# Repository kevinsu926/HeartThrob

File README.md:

# Heartthrob

A heart-shaped ECG board that turns your heartbeat into sound. Touch the two gold electrodes and it plays your ECG as a high-pitched tone, which a phone or laptop can decode using its microphone. It has no Bluetooth, no Wi-Fi and no firmware. 

## How it works

```mermaid
flowchart LR
    A[Fingers on<br/>electrodes] --> B[AD8233<br/>ECG amplifier]
    B --> C[LTC6990<br/>oscillator]
    C --> D[Piezo<br/>~18.5 kHz tone]
    D --> E[Phone / laptop<br/>microphone]
```

1. **Pick up the signal.** One finger from each hand rests on the gold electrodes on each side of the heart. The tiny voltage your heart produces appears between them.
2. **Amplify it.** An AD8233 ECG chip amplifies and filters that signal into a clean waveform.
3. **Turn it into a tone.** The waveform controls an LTC6990 oscillator, so the pitch of an 18.5 kHz tone rises and falls with each heartbeat.
4. **Play it.** A small piezo plays the tone. It is high enough that most adults can't hear it, but phone microphones can.
5. **Decode it.** A phone or laptop listens to the tone, tracks its pitch, and turns it back into a live ECG trace and heart rate.

<p align="center">
  <picture>
    <source media="(prefers-color-scheme: dark)" srcset="hardware/Heartthrob/illustrations/sample-waveform-dark.png">
    
  </picture>
</p>

The top trace is what the phone shows: P, QRS and T waves for each beat, with heart rate taken from the time between R peaks. The bottom trace is the same signal as the microphone hears it: a tone near 18.5 kHz whose pitch rises and falls with the ECG. (Simulated example.)

When nobody is touching the electrodes, the board detects that the leads are off and switches the oscillator off to save battery. 

## Power

The board runs on a small 1S LiPo battery soldered to pads on the back, and charges over USB-C. A 3.0 V regulator powers the circuit, and a P-FET protects it if the battery is connected backwards.

## Project structure

- `hardware/Heartthrob/`
  KiCad 10 project: schematic, 4-layer PCB layout, design rules and custom footprints. Open `Heartthrob.kicad_pro`.
- `hardware/Heartthrob/Render/`
  3D renders of the front and back.
- `hardware/Heartthrob/Documentation/`
  Schematic PDF, per-layer PCB plots, and earlier design snapshots in `Archive/`.
- `hardware/Heartthrob/illustrations/`
  Figures used in this README.

> **Note:** This is a hobby project, not a medical device. Don't use it for diagnosis, and don't wear it while it's plugged in to charge.

## Credits

Based on [SiBowald's ECG PCB business card](https://github.com/SiBowald/ecg-pcb-business-card), redesigned by Kevin Su as a rechargeable, heart-shaped board.

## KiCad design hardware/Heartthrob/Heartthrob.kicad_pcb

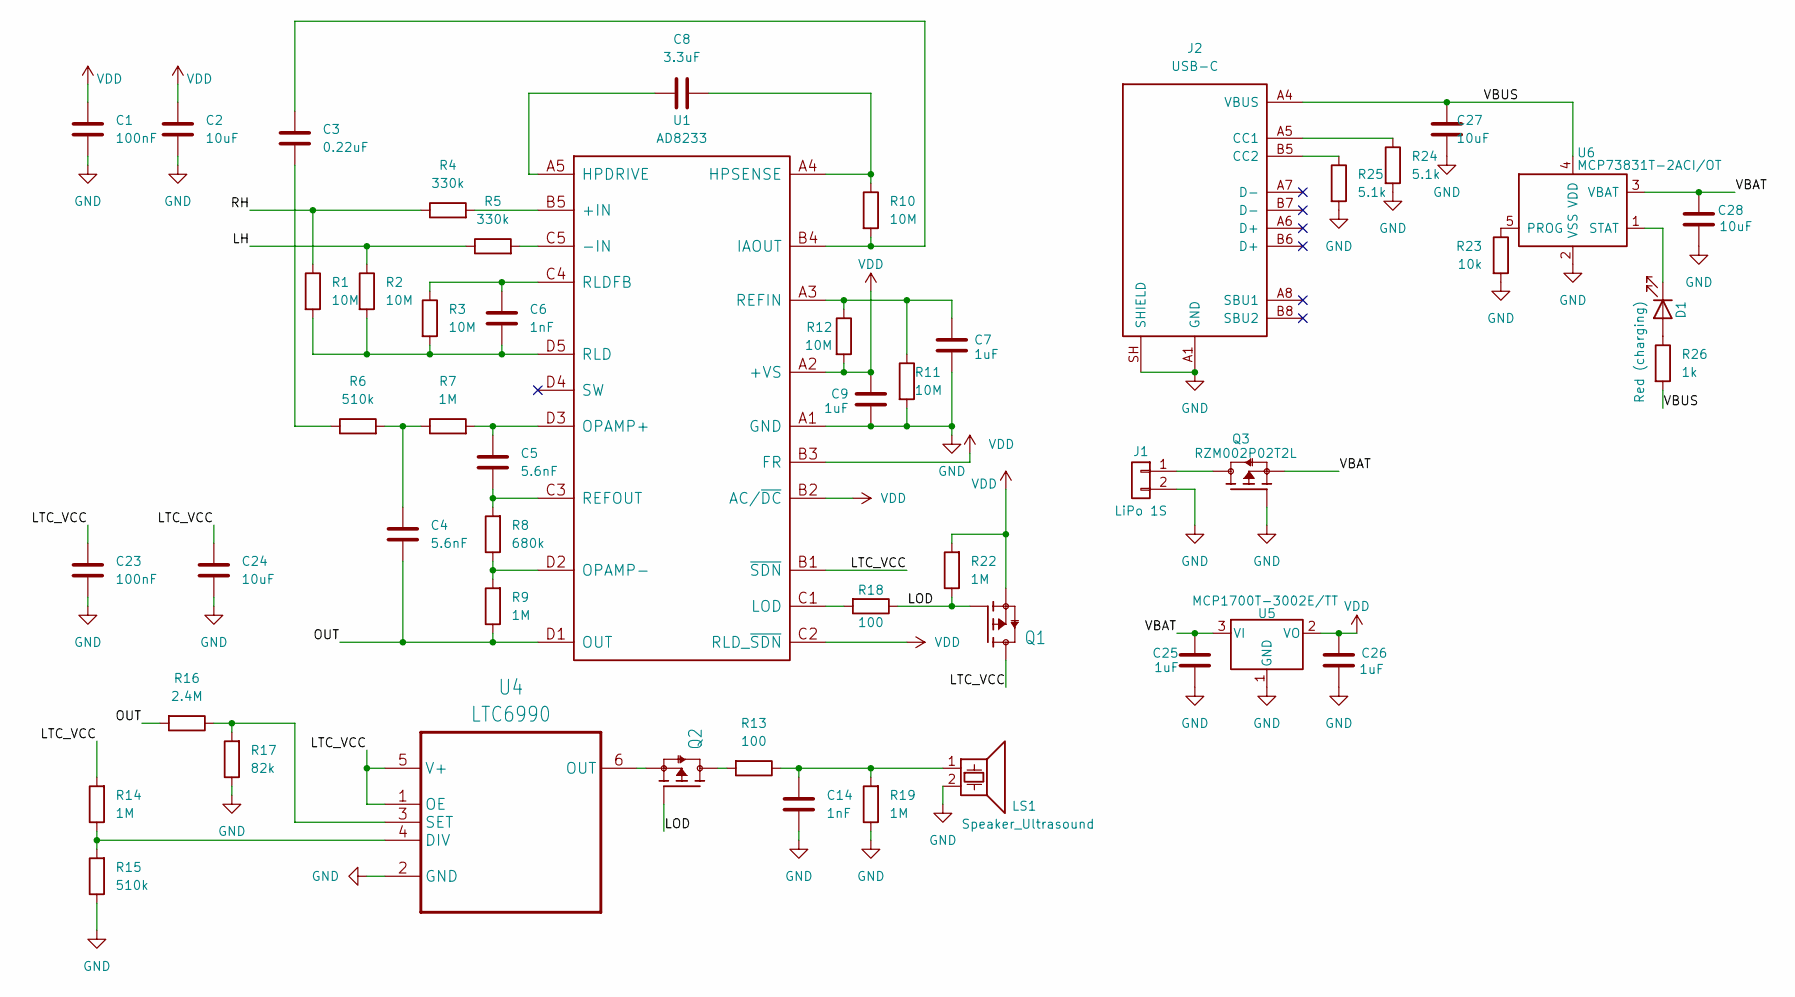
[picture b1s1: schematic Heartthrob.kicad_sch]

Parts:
C1, C23: 100nF; C_0402_1005Metric; Part Name 100nF 16V Ceramic Cap; LCSC C85857
C2, C24, C27, C28: 10uF; C_0402_1005Metric; Part Name 10uF 6.3V Ceramic Cap; LCSC C412251
C3: 0.22uF; C_0402_1005Metric; Part Name 220nF 16V Ceramic Cap; LCSC C126524
C4, C5: 5.6nF; C_0402_1005Metric; Part Name CAP CER 5.6nF 50V C0G 0402; LCSC C3878619
C6, C14: 1nF; C_0402_1005Metric; Part Name 1nF 50V Ceramic Cap; LCSC C76947
C7, C9, C25, C26: 1uF; C_0402_1005Metric; Part Name 1uF 6.3V Ceramic Cap; LCSC C2167130
C8: 3.3uF; C_0402_1005Metric; Part Name 10V 3.3uF X5R ±10% 0402 Ceramic Capacit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; LCSC C695126
D1: Red (charging); LED_0603_1608Metric; Part Number KT-0603R; LCSC C2286
J1: LiPo 1S; LiPo_SMD_Pads_2x3mm_P4mm
J2: USB-C; USB_C_Receptacle_HRO_TYPE-C-31-M-12; Part Number TYPE-C-31-M-12
LS1: Speaker_Ultrasound; Piezo_12mm; Part Name BUZZER ELEMENT STD 18.5 KHZ 12MM
Q1, Q2, Q3: RZM002P02T2L; SOT-723; Part Name MOSFET P-CH 20V 200MA VMT3
R1, R2, R3, R10, R11, R12: 10M; R_0201_0603Metric; Part Name 10M Film Resistor ±1% 0,05W; LCSC C469663
R4, R5: 330k; R_0201_0603Metric; Part Name 330KΩ ±1% 1/20W ±200ppm/℃; LCSC C142017
R6, R15: 510k; R_0201_0603Metric; Part Name 510KΩ ±1% 1/20W ±200ppm/℃; LCSC C295805
R7, R9, R14, R19, R22: 1M; R_0201_0603Metric; Part Name 1M Film Resistor ±1% 1/20W ±200ppm/℃; LCSC C295786
R8: 680k; R_0201_0603Metric; Part Name 680KΩ ±1% 1/20W ±200ppm/℃; LCSC C226598
R13, R18: 100; R_0201_0603Metric; Part Name 100Ω ±1% 1/20W ±200ppm/℃; LCSC C77623
R16: 2.4M; R_0201_0603Metric; Part Name 2.4M Film Resistor ±1% 50mW; LCSC C474580
R17: 82k; R_0201_0603Metric; Part Name 82k Film Resistor ±1% 1/20W ±200ppm/℃; LCSC C273288
R23: 10k; R_0201_0603Metric; Part Number RC0201FR-0710KL; LCSC C106225
R24, R25: 5.1k; R_0201_0603Metric; Part Number RC0201FR-075K1L; LCSC C274341
R26: 1k; R_0201_0603Metric; Part Number RC0201FR-071KL; LCSC C138165
U1: AD8233; 20-WLCPS-2MMX1.7MM
U4: LTC6990; SOT95P280X100-6N; Part Name Oszillator - Silizium IC 488Hz bis 2MHz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; LCSC C581032
U5: MCP1700T-3002E/TT; SOT-23; Part Number MCP1700T-3002E/TT
U6: MCP73831T-2ACI/OT; SOT-23-5; Part Number MCP73831T-2ACI/OT

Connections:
/LH: R2.1, R5.1
/LOD: Q1.1 (G), Q2.1 (G), R18.1, R22.1
/LTC_VCC: C23.2, C24.2, Q1.3 (D), R14.2, U1.B1 (~SDN), U4.1 (OE), U4.5 (V+)
/OUT: C4.1, R9.1, R16.2, U1.D1 (OUT)
/RH: R1.1, R4.1
/VBAT: C25.1, C28.1, Q3.2 (S), U5.3 (VI), U6.3 (VBAT)
/VBUS: C27.1, J2.A4 (VBUS), J2.A9 (VBUS), J2.B4 (VBUS), J2.B9 (VBUS), R26.2, U6.4 (VDD)
GND: C1.1, C2.1, C7.1, C9.1, C14.1, C23.1, C24.1, C25.2, C26.2, C27.2, C28.2, J1.2, J2.A1 (GND), J2.A12 (GND), J2.B1 (GND), J2.B12 (GND), J2.SH (SHIELD), LS1.2, Q3.1 (G), R11.2, R15.1, R17.1, R19.1, R23.2, R24.2, R25.2, U1.A1 (GND), U4.2 (GND), U5.1 (GND), U6.2 (VSS)
unnamed: C3.1, R6.1
unnamed: C4.2, R6.2, R7.1
unnamed: C14.2, LS1.1, R13.1, R19.2
unnamed: D1.2 (A), R26.1
unnamed: D1.1 (K), U6.1 (STAT)
unnamed: J1.1, Q3.3 (D)
unnamed: J2.A5 (CC1), R24.1
unnamed: J2.B5 (CC2), R25.1
unnamed: Q2.3 (D), R13.2
unnamed: Q2.2 (S), U4.6 (OUT)
unnamed: R4.2, U1.B5 (+IN)
unnamed: R5.2, U1.C5 (-IN)
unnamed: C8.1, U1.A5 (HPDRIVE)
unnamed: C8.2, R10.1, U1.A4 (HPSENSE)
unnamed: C3.2, R10.2, U1.B4 (IAOUT)
unnamed: R18.2, U1.C1 (LOD)
unnamed: C5.2, R7.2, U1.D3 (OPAMP+)
unnamed: R8.1, R9.2, U1.D2 (OPAMP-)
unnamed: C7.2, R11.1, R12.1, U1.A3 (REFIN)
unnamed: C5.1, R8.2, U1.C3 (REFOUT)
unnamed: C6.1, R1.2, R2.2, R3.2, U1.D5 (RLD)
unnamed: C6.2, R3.1, U1.C4 (RLDFB)
unnamed: R14.1, R15.2, U4.4 (DIV)
unnamed: R16.1, R17.2, U4.3 (SET)
unnamed: R23.1, U6.5 (PROG)
VDD: C1.2, C2.2, C9.2, C26.1, Q1.2 (S), R12.2, R22.2, U1.A2 (+VS), U1.B2 (AC/~DC), U1.B3 (FR), U1.C2 (RLD_~SDN), U5.2 (VO)

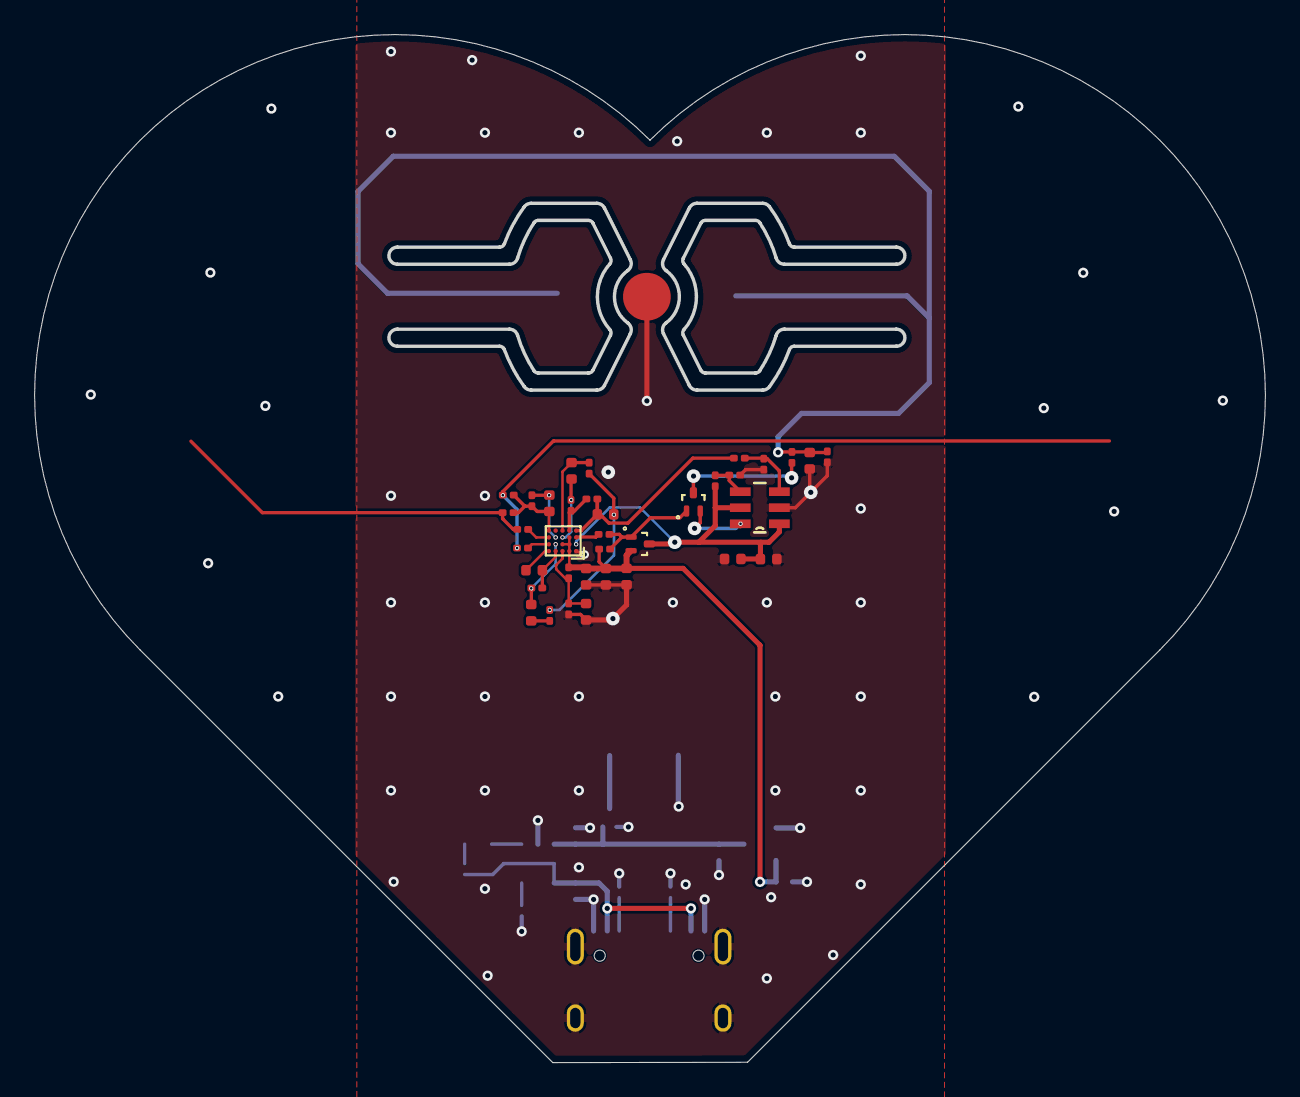
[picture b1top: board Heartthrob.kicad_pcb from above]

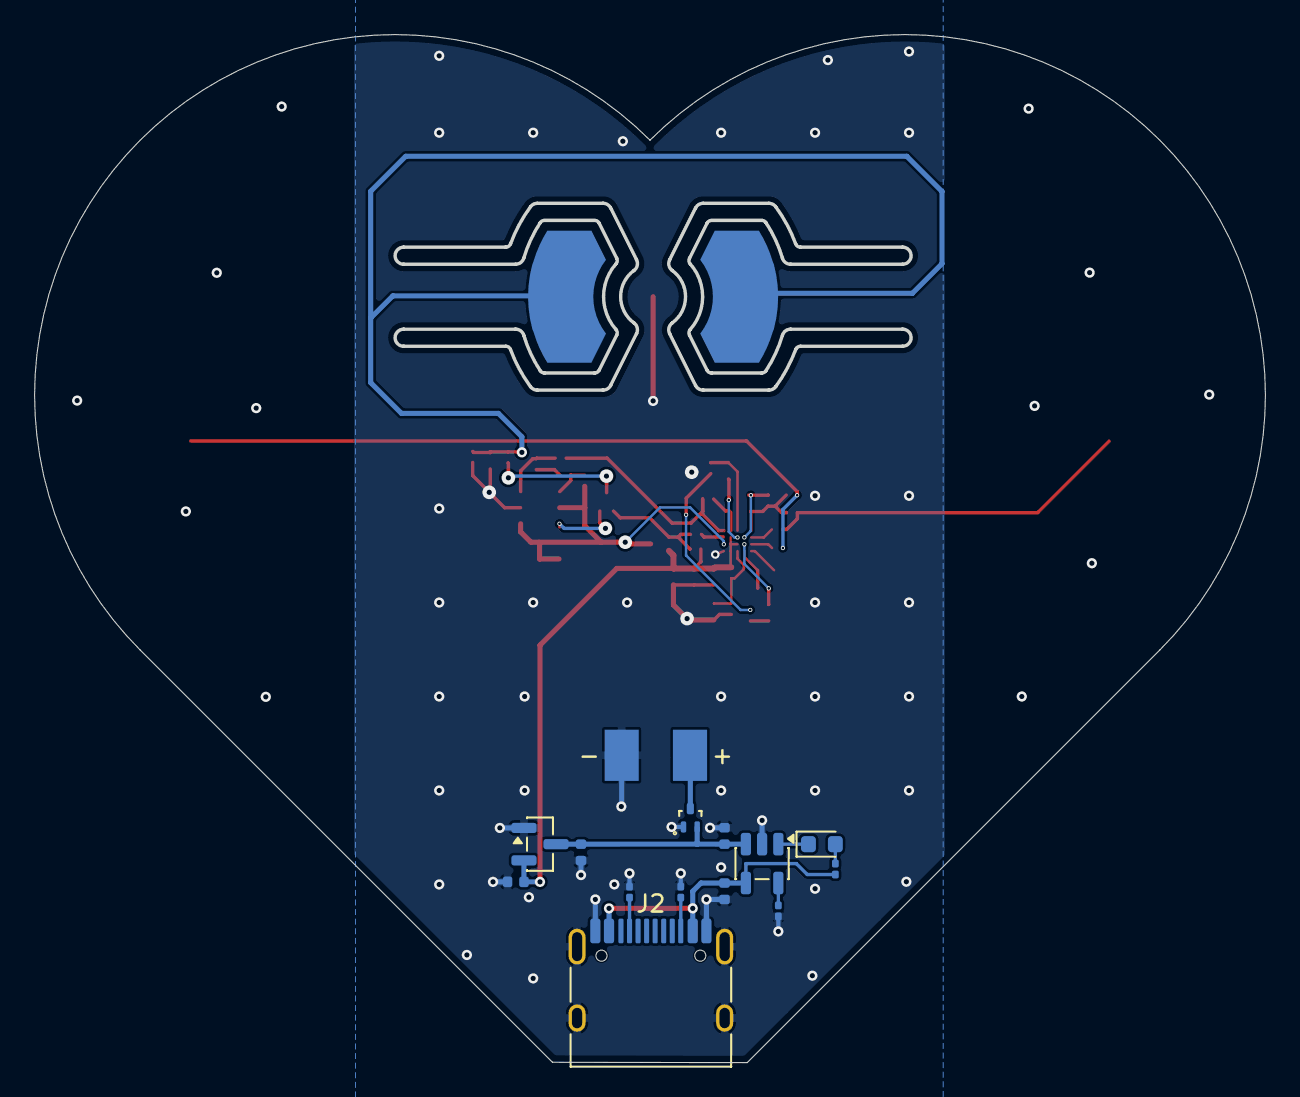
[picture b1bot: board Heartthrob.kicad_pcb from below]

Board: 4 copper layers, 72.0 x 60.2 mm, 51 parts (14 on the bottom side), 34 nets.
